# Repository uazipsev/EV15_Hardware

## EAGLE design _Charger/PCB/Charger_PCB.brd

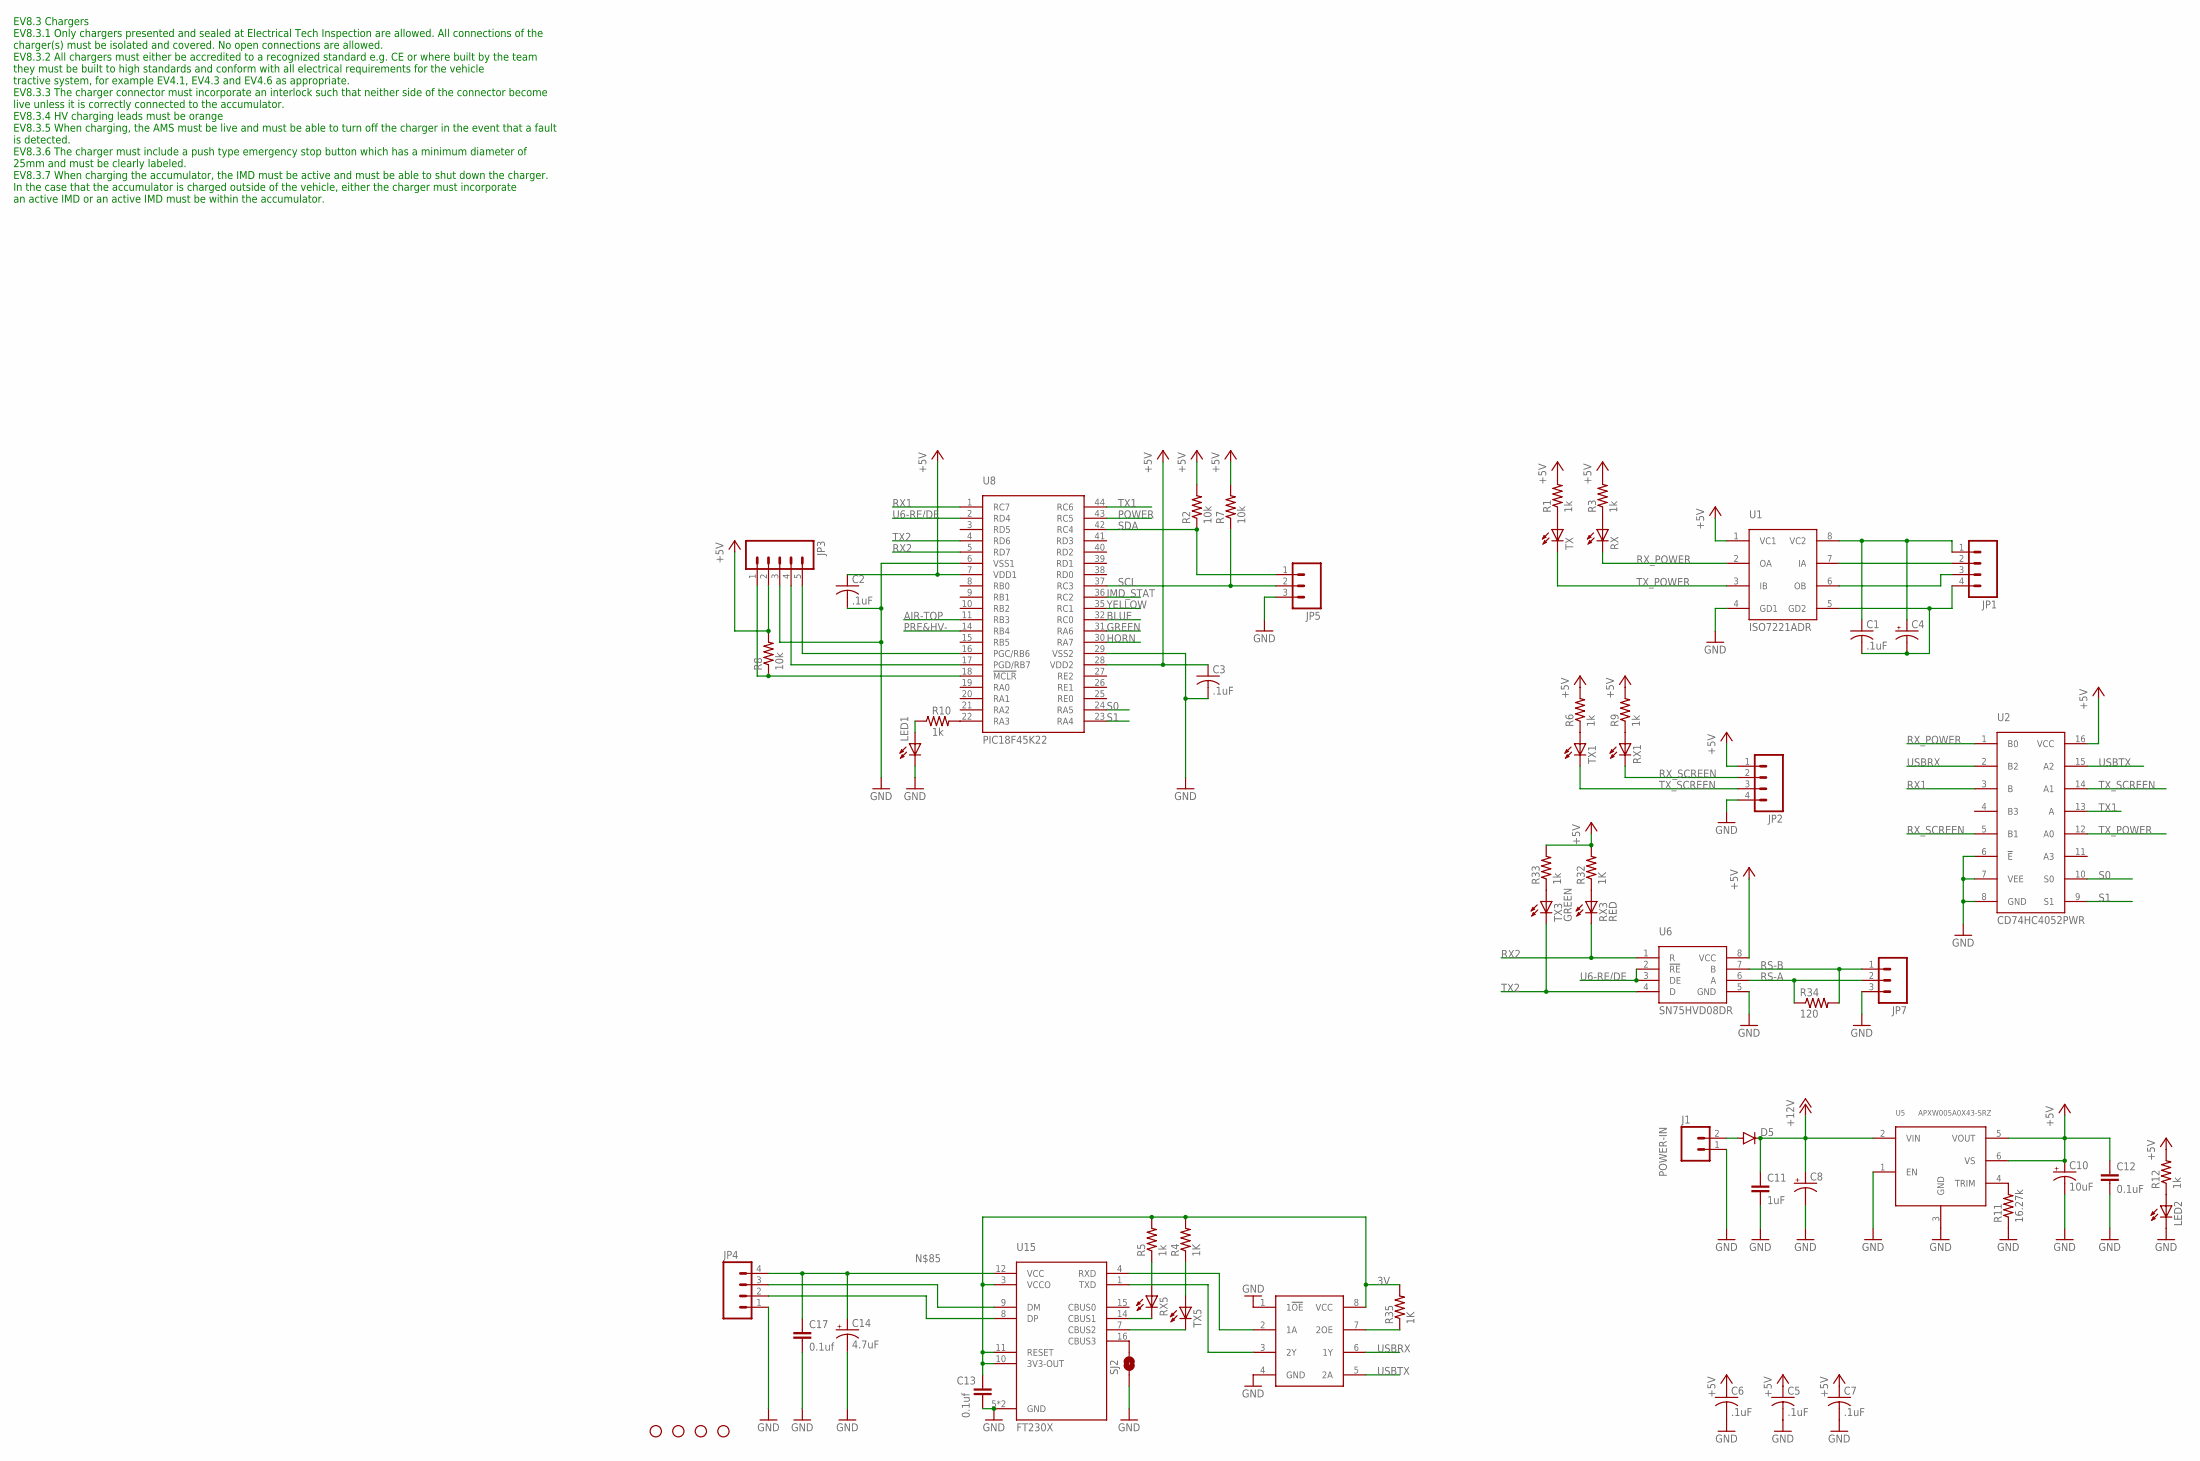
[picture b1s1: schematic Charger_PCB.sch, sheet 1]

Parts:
C1, C2, C3, C5, C6, C7: .1uF; C0805
C4: CAP_POL1206-KIT; EIA3216-KIT
C8: CAP_POLE; PANASONIC_E
C10: 10uF; EIA6032
C11: 1uF; 1206
C12: 0.1uF; 0805
C13, C17: 0.1uf; 0805
C14: 4.7uF; EIA3216
D5: DIODEHV; DIODE-HV
J1: POWER-IN; M2
JP1, JP2, JP4: M04POLAR_LOCK; MOLEX-1X4_LOCK
JP3: M05LOCK_LONGPADS; 1X05_LOCK_LONGPADS
JP5, JP7: M03POLAR_LOCK; MOLEX-1X3_LOCK
LED1: LEDCHIP-LED0805; CHIP-LED0805
LED2: LEDCHIPLED_0805; CHIPLED_0805
R1, R3, R5, R6, R9, R10, R12, R33: 1k; R0805
R2, R7: 10k; R0805
R4, R32, R35: 1K; R0805
R8: 10k; 0805
R11: 16.27k; R0805
R34: 120; R0805
RX, RX1, RX5: LEDCHIPLED_0805; CHIPLED_0805
RX3: RED; CHIPLED_0805
SJ2: JUMPER-PAD-2-NOYES_SILK; PAD-JUMPER-2-NO_YES_SILK
STANDOFF1, STANDOFF2, STANDOFF3, STANDOFF4: STAND-OFF
TX, TX1, TX5: LEDCHIPLED_0805; CHIPLED_0805
TX3: GREEN; CHIPLED_0805
U1: ISO7221ADR; SO08
U2: CD74HC4052PWR; TSSOP-16
U4: SN74LVC2G241DCTR; VFSOP-8
U5: APXW005A0X43-SRZ
U6: SN75HVD08DR; SO-8
U8: PIC18F45K22; TQFP-44
U15: FT230X; SSOP-16

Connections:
3V: C13.1, R4.2, R5.2, R35.2, U4.8 (VCC), U15.3 (VCCO), U15.10 (3V3-OUT), U15.11 (RESET)
+5V: C2.1, C3.1, C5.1, C6.1, C7.1, C10.P$1 (+), C12.1, JP2.1, JP3.2, R1.2, R2.2, R3.2, R6.2, R7.2, R8.2, R9.2, R12.2, R32.2, R33.2, U1.1 (VC1), U2.16 (VCC), U5.5 (VOUT), U5.6 (VS), U6.8 (VCC), U8.7 (VDD1), U8.28 (VDD2); also elsewhere on the board
+12V: C8.+, C11.1, D5.C, U5.2 (VIN); also elsewhere on the board
AIR-TOP: U8.11 (RB3); also elsewhere on the board
BLUE: U8.32 (RC0); also elsewhere on the board
GND: C2.2, C3.2, C5.2, C6.2, C7.2, C8.-, C10.P$2 (-), C11.2, C12.2, C13.2, C14.C (-), C17.2, J1.1, JP2.4, JP3.3, JP4.1, JP5.3, JP7.3, LED1.C, LED2.C, R11.1, SJ2.1, U1.4 (GD1), U2.6 (!E), U2.7 (VEE), U2.8 (GND), U4.1 (1!OE), U4.4 (GND), U5.1 (EN), U5.3 (GND), U6.5 (GND), U8.6 (VSS1), U8.29 (VSS2), U15.5 (GND), U15.13 (GND); also elsewhere on the board
GREEN: U8.31 (RA6); also elsewhere on the board
HORN: U8.30 (RA7); also elsewhere on the board
IMD_STAT: U8.36 (RC2); also elsewhere on the board
unnamed: LED1.A, R10.1
unnamed: R10.2, U8.22 (RA3)
unnamed: C1.1, C4.A (+), JP1.1, U1.8 (VC2)
unnamed: JP1.2, U1.7 (IA)
unnamed: JP1.3, U1.6 (OB)
unnamed: C1.2, C4.C (-), JP1.4, U1.5 (GD2)
unnamed: R1.1, TX.A
unnamed: R3.1, RX.A
unnamed: R4.1, TX5.A
unnamed: R5.1, RX5.A
unnamed: R6.1, TX1.A
unnamed: R9.1, RX1.A
unnamed: R11.2, U5.4 (TRIM)
unnamed: LED2.A, R12.1
unnamed: R33.1, TX3.A
unnamed: TX5.C, U15.7 (CBUS2)
unnamed: R32.1, RX3.A
unnamed: RX5.C, U15.14 (CBUS1)
unnamed: U4.2 (1A), U15.4 (RXD)
unnamed: JP3.4, U8.17 (PGD/RB7)
unnamed: U4.3 (2Y), U15.1 (TXD)
unnamed: JP4.3, U15.9 (DM)
unnamed: JP3.5, U8.16 (PGC/RB6)
unnamed: D5.A, J1.2
unnamed: JP3.1, R8.1, U8.18 (!MCLR)
unnamed: JP4.2, U15.8 (DP)
unnamed: SJ2.2, U15.16 (CBUS3)
unnamed: R35.1, U4.7 (2OE)
unnamed: C14.A (+), C17.1, JP4.4, U15.12 (VCC)
POWER: U8.43 (RC5); also elsewhere on the board
PRE&HV-: U8.14 (RB4); also elsewhere on the board
RS-A: JP7.2, R34.1, U6.6 (A)
RS-B: JP7.1, R34.2, U6.7 (B)
RX1: U2.3 (B), U8.1 (RC7)
RX2: RX3.C, U6.1 (R), U8.5 (RD7)
RX_POWER: RX.C, U1.2 (OA), U2.1 (B0)
RX_SCREEN: JP2.2, RX1.C, U2.5 (B1)
S0: U2.10 (S0), U8.24 (RA5)
S1: U2.9 (S1), U8.23 (RA4)
SCL: JP5.2, R7.1, U8.37 (RC3)
SDA: JP5.1, R2.1, U8.42 (RC4)
TX1: U2.13 (A), U8.44 (RC6)
TX2: TX3.C, U6.4 (D), U8.4 (RD6)
TX_POWER: TX.C, U1.3 (IB), U2.12 (A0)
TX_SCREEN: JP2.3, TX1.C, U2.14 (A1)
U6-RE/DE: U6.2 (!RE), U6.3 (DE), U8.2 (RD4)
USBRX: U2.2 (B2), U4.6 (1Y)
USBTX: U2.15 (A2), U4.5 (2A)
YELLOW: U8.35 (RC1); also elsewhere on the board

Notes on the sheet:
EV8.3 Chargers EV8.3.1 Only chargers presented and sealed at Electrical Tech Inspection are allowed. All connections of the charger(s) must be isolated and covered. No open connections are allowed. EV8.3.2 All chargers must either be accredited to a recognized standard e.g. CE or where built by the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

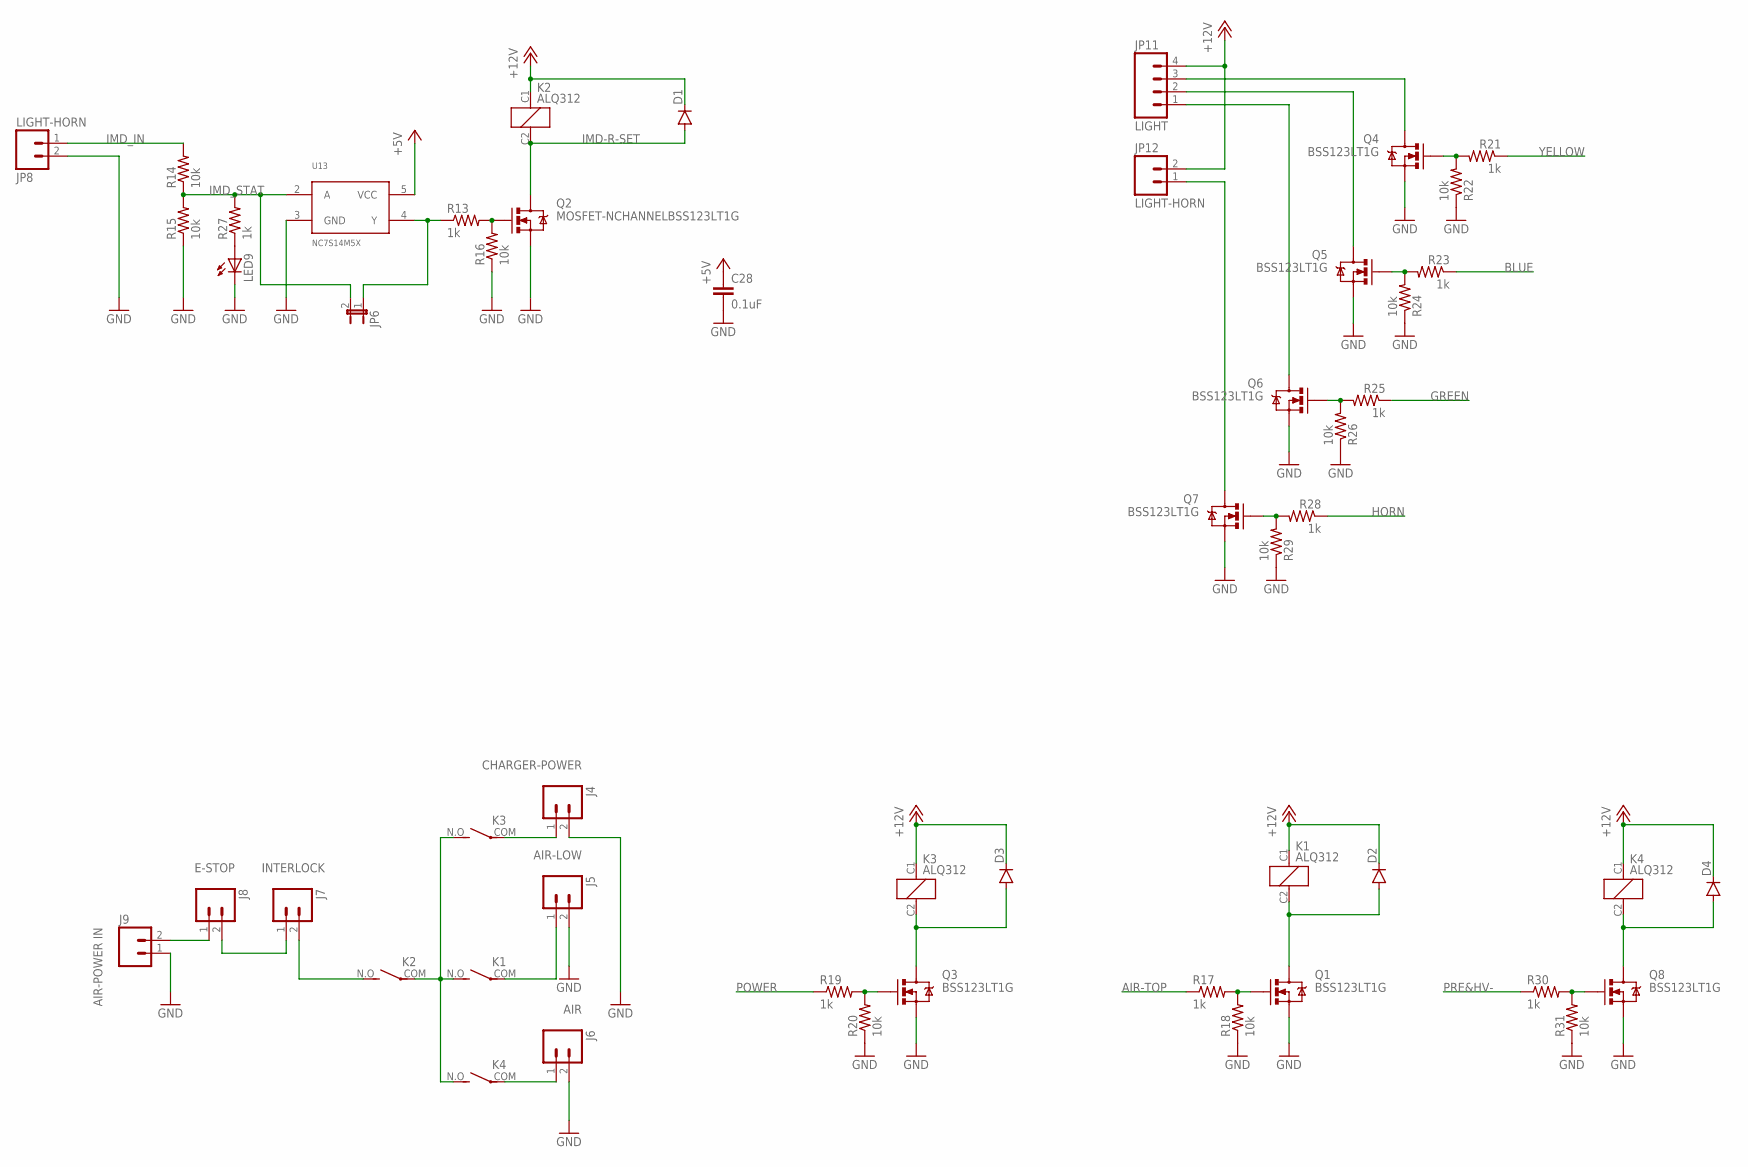
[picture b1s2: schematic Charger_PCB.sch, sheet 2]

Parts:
C28: 0.1uF; 0805
D1, D2, D3, D4: DIODEHV; DIODE-HV
J4: CHARGER-POWER; M2
J5: AIR-LOW; M2
J6: AIR; M2
J7: INTERLOCK; M2
J8: E-STOP; M2
J9: AIR-POWER IN; M2
JP6: JUMPER-2SMD-NO; SJ_2S-NO
JP8, JP12: LIGHT-HORN; MOLEX-1X2_LOCK
JP11: LIGHT; MOLEX-1X4_LOCK
K1, K2, K3, K4: ALQ312
LED9: LEDCHIPLED_0805; CHIPLED_0805
Q1, Q3, Q4, Q5, Q6, Q7, Q8: BSS123LT1G; SOT23
Q2: MOSFET-NCHANNELBSS123LT1G; SOT23
R13, R17, R19, R21, R23, R25, R27, R28, R30: 1k; 0805
R14, R15, R16, R18, R20, R22, R24, R26, R29, R31: 10k; 0805
U13: NC7S14M5X; SOT23-5

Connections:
+5V: C28.1, U13.5 (VCC); also elsewhere on the board
+12V: D1.C, D2.C, D3.C, D4.C, JP11.4, JP12.2, K1.C1 (+), K2.C1 (+), K3.C1 (+), K4.C1 (+); also elsewhere on the board
AIR-TOP: R17.1; also elsewhere on the board
BLUE: R23.1; also elsewhere on the board
GND: C28.2, J4.2, J5.2, J6.2, J9.1, JP8.2, LED9.C, Q1.2 (S), Q2.2 (S), Q3.2 (S), Q4.2 (S), Q5.2 (S), Q6.2 (S), Q7.2 (S), Q8.2 (S), R15.1, R16.1, R18.1, R20.1, R22.1, R24.1, R26.1, R29.1, R31.1, U13.3 (GND); also elsewhere on the board
GREEN: R25.1; also elsewhere on the board
HORN: R28.1; also elsewhere on the board
IMD-R-SET: D1.A, K2.C2 (-), Q2.3 (D)
IMD-R-SET1: D2.A, K1.C2 (-), Q1.3 (D)
IMD-R-SET2: D3.A, K3.C2 (-), Q3.3 (D)
IMD-R-SET3: D4.A, K4.C2 (-), Q8.3 (D)
IMD_IN: JP8.1, R14.2
IMD_STAT: JP6.2, R14.1, R15.2, R27.2, U13.2 (A); also elsewhere on the board
unnamed: K1.N.O (S), K2.COM, K3.N.O (S), K4.N.O (S)
unnamed: Q2.1 (G), R13.2, R16.2
unnamed: Q8.1 (G), R30.2, R31.2
unnamed: J8.1, J9.2
unnamed: J7.1, J8.2
unnamed: J4.1, K3.COM
unnamed: Q4.1 (G), R21.2, R22.2
unnamed: J6.1, K4.COM
unnamed: Q1.1 (G), R17.2, R18.2
unnamed: Q3.1 (G), R19.2, R20.2
unnamed: Q5.1 (G), R23.2, R24.2
unnamed: Q6.1 (G), R25.2, R26.2
unnamed: Q7.1 (G), R28.2, R29.2
unnamed: JP11.3, Q4.3 (D)
unnamed: JP11.2, Q5.3 (D)
unnamed: JP11.1, Q6.3 (D)
unnamed: JP6.1, R13.1, U13.4 (Y)
unnamed: LED9.A, R27.1
unnamed: JP12.1, Q7.3 (D)
unnamed: J5.1, K1.COM
unnamed: J7.2, K2.N.O (S)
POWER: R19.1; also elsewhere on the board
PRE&HV-: R30.1; also elsewhere on the board
YELLOW: R21.1; also elsewhere on the board

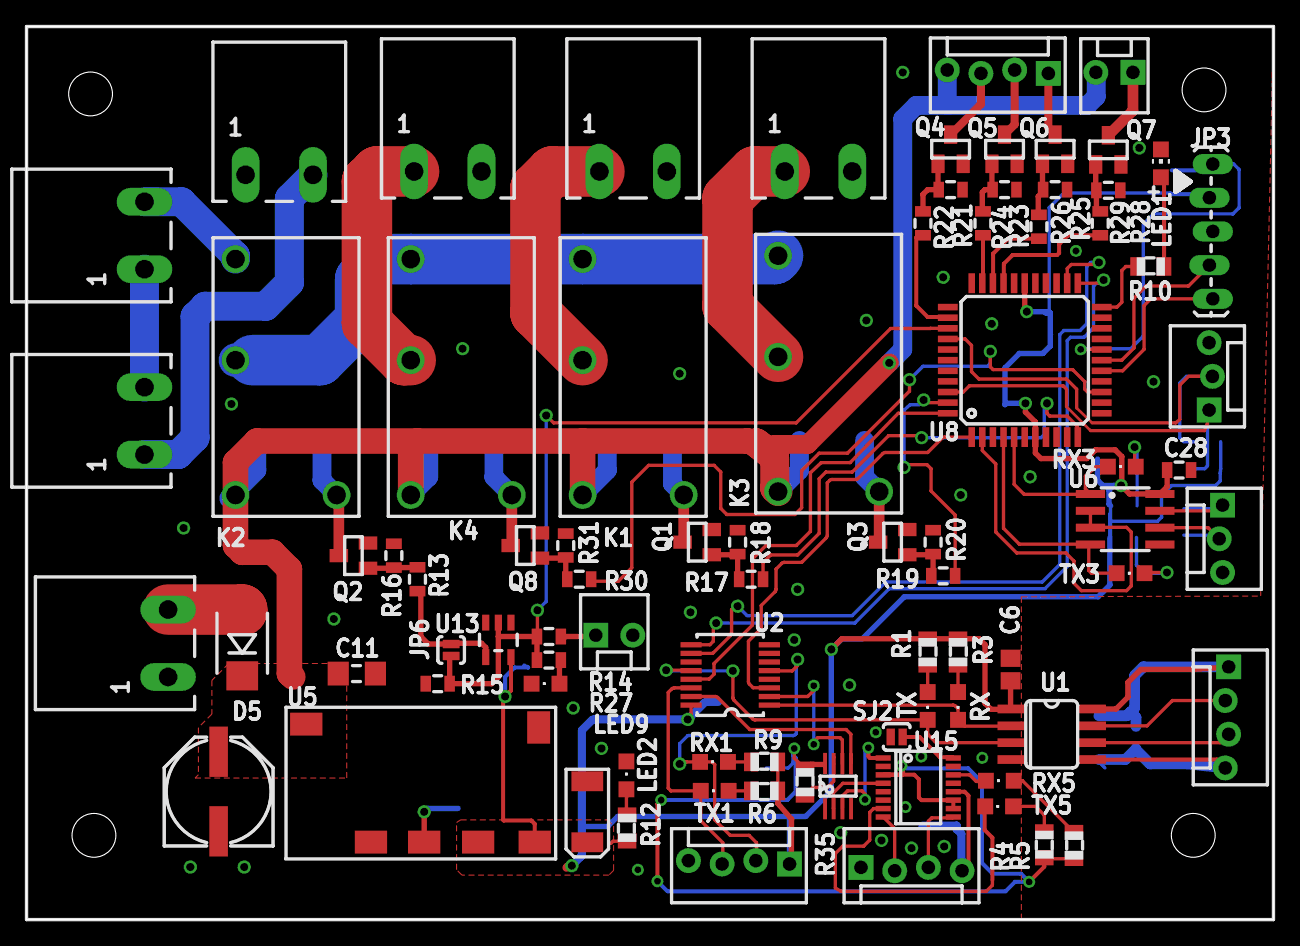
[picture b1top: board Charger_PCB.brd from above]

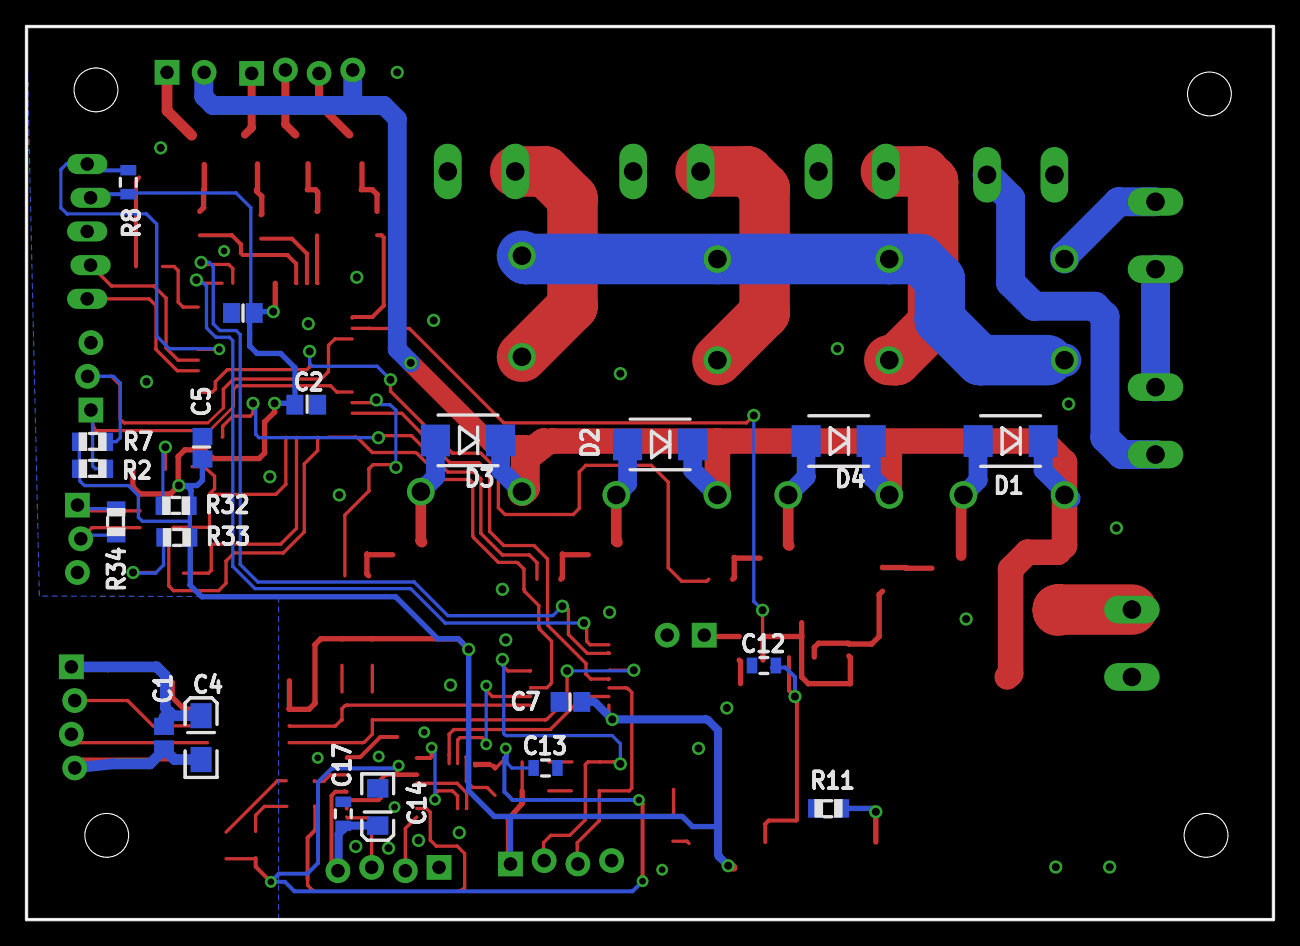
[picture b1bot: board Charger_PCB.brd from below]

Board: 2 copper layers, 94.0 x 67.3 mm, 108 parts (21 on the bottom side), 84 nets.

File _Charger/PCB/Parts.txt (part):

Partlist

Exported from Charger_PCB.sch at 5/25/2015 11:38:13 PM

EAGLE Version 6.6.0 Copyright (c) 1988-2014 CadSoft

Assembly variant: 

Part     Value                     Device                    Package                  Library               Sheet

C1       .1uF                      C-USC0805                 C0805                    adafruit              1
C2       .1uF                      C-USC0805                 C0805                    adafruit              1
C3       .1uF                      C-USC0805                 C0805                    adafruit              1
C4                                 CAP_POL1206-KIT           EIA3216-KIT              SparkFun-Passives     1
C5       .1uF                      C-USC0805                 C0805                    adafruit              1
C6       .1uF                      C-USC0805                 C0805                    adafruit              1
C7       .1uF                      C-USC0805                 C0805                    adafruit              1
C8                                 CAP_POLE                  PANASONIC_E              SparkFun-Capacitors   1
C10      10uF                      CAP_POL6032               EIA6032                  SparkFun-Capacitors   1
C11      1uF                       CAP1206                   1206                     SparkFun-Capacitors   1
C12      0.1uF                     CAP0805                   0805                     SparkFun-Capacitors   1
C13      0.1uf                     CAP0805                   0805                     SparkFun              1
C14      4.7uF                     CAP_POL1206               EIA3216                  SparkFun              1
C17      0.1uf                     CAP0805                   0805                     SparkFun              1
C28      0.1uF                     CAP0805                   0805                     SparkFun-Passives     2
D1                                 DIODEHV                   DIODE-HV                 SparkFun-DiscreteSemi 2
D2                                 DIODEHV                   DIODE-HV                 SparkFun-DiscreteSemi 2
D3                                 DIODEHV                   DIODE-HV                 SparkFun-DiscreteSemi 2
D4                                 DIODEHV                   DIODE-HV                 SparkFun-DiscreteSemi 2
D5                                 DIODEHV                   DIODE-HV                 SparkFun-DiscreteSemi 1
J1       POWER-IN                  EUROMAG-290DEG            M2                       NASA_LIB              1
J4       CHARGER-POWER             EUROMAG-290DEG            M2                       NASA_LIB              2
J5       AIR-LOW                   EUROMAG-290DEG            M2                       NASA_LIB              2
J6       AIR                       EUROMAG-290DEG            M2                       NASA_LIB              2
J7       INTERLOCK                 EUROMAG-290DEG            M2                       NASA_LIB              2
J8       E-STOP                    EUROMAG-290DEG            M2                       NASA_LIB              2
J9       AIR-POWER IN              EUROMAG-290DEG            M2                       NASA_LIB              2
JP1                                M04POLAR_LOCK             MOLEX-1X4_LOCK           SparkFun-Connectors   1
JP2                                M04POLAR_LOCK             MOLEX-1X4_LOCK           SparkFun-Connectors   1
JP3                                M05LOCK_LONGPADS          1X05_LOCK_LONGPADS       SparkFun-Connectors   1
JP4                                M04POLAR_LOCK             MOLEX-1X4_LOCK           SparkFun-Connectors   1
JP5                                M03POLAR_LOCK             MOLEX-1X3_LOCK           SparkFun-Connectors   1
JP6                                JUMPER-2SMD-NO            SJ_2S-NO                 SparkFun-Passives     2
JP7                                M03POLAR_LOCK             MOLEX-1X3_LOCK           SparkFun-Connectors   1
JP8      LIGHT-HORN                M02POLAR_LOCK             MOLEX-1X2_LOCK           SparkFun-Connectors   2
JP11     LIGHT                     M04POLAR_LOCK             MOLEX-1X4_LOCK           SparkFun-Connectors   2
JP12     LIGHT-HORN                M02POLAR_LOCK             MOLEX-1X2_LOCK           SparkFun-Connectors   2
K1       ALQ312                    ALQ312                    ALQ312                   FSAE Eletric (2)      2
K2       ALQ312                    ALQ312                    ALQ312                   FSAE Eletric (2)      2
K3       ALQ312                    ALQ312                    ALQ312                   FSAE Eletric (2)      2
K4       ALQ312                    ALQ312                    ALQ312                   FSAE Eletric          2
LED1                               LEDCHIP-LED0805           CHIP-LED0805             adafruit              1
LED2                               LEDCHIPLED_0805           CHIPLED_0805             adafruit              1
LED9                               LEDCHIPLED_0805           CHIPLED_0805             adafruit              2
Q1       BSS123LT1G                MOSFET-NCHANNELBSS123LT1G SOT23                    SparkFun-DiscreteSemi 2
Q2       MOSFET-NCHANNELBSS123LT1G MOSFET-NCHANNELBSS123LT1G SOT23                    SparkFun-DiscreteSemi 2
Q3       BSS123LT1G                MOSFET-NCHANNELBSS123LT1G SOT23                    SparkFun-DiscreteSemi 2
Q4       BSS123LT1G                MOSFET-NCHANNELBSS123LT1G SOT23                    SparkFun-DiscreteSemi 2
Q5       BSS123LT1G                MOSFET-NCHANNELBSS123LT1G SOT23                    SparkFun-DiscreteSemi 2
Q6       BSS123LT1G                MOSFET-NCHANNELBSS123LT1G SOT23                    SparkFun-DiscreteSemi 2
Q7       BSS123LT1G                MOSFET-NCHANNELBSS123LT1G SOT23                    SparkFun-DiscreteSemi 2
Q8       BSS123LT1G                MOSFET-NCHANNELBSS123LT1G SOT23                    SparkFun-DiscreteSemi 2
R1       1k                        R-US_R0805                R0805                    adafruit              1
R2       2k                        R-US_R0805                R0805                    adafruit              1
R3       1k                        R-US_R0805                R0805                    adafruit              1
R4       1K                        R-US_R0805                R0805                    adafruit              1
R5       1k                        R-US_R0805                R0805                    adafruit              1
R6       1k                        R-US_R0805                R0805                    adafruit              1
R7       2k                        R-US_R0805                R0805                    adafruit              1
R8       10k                       RESISTOR0805-RES          0805                     SparkFun-Passives     1
R9       1k                        R-US_R0805                R0805                    adafruit              1
R10      1k                        R-US_R0805                R0805                    adafruit              1
R11      16.27k                    R-US_R0805                R0805                    adafruit              1
R12      1k                        R-US_R0805                R0805                    adafruit              1
R13      1k                        RESISTOR0805-RES          0805                     SparkFun-Passives     2
R14      5k                        RESISTOR0805-RES          0805                     SparkFun-Passives     2
R15      5k                        RESISTOR0805-RES          0805                     SparkFun-Passives     2
R16      10k                       RESISTOR0805-RES          0805                     SparkFun-Passives     2
R17      1k                        RESISTOR0805-RES          0805                     SparkFun-Passives     2
R18      10k                       RESISTOR0805-RES          0805                     SparkFun-Passives     2
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
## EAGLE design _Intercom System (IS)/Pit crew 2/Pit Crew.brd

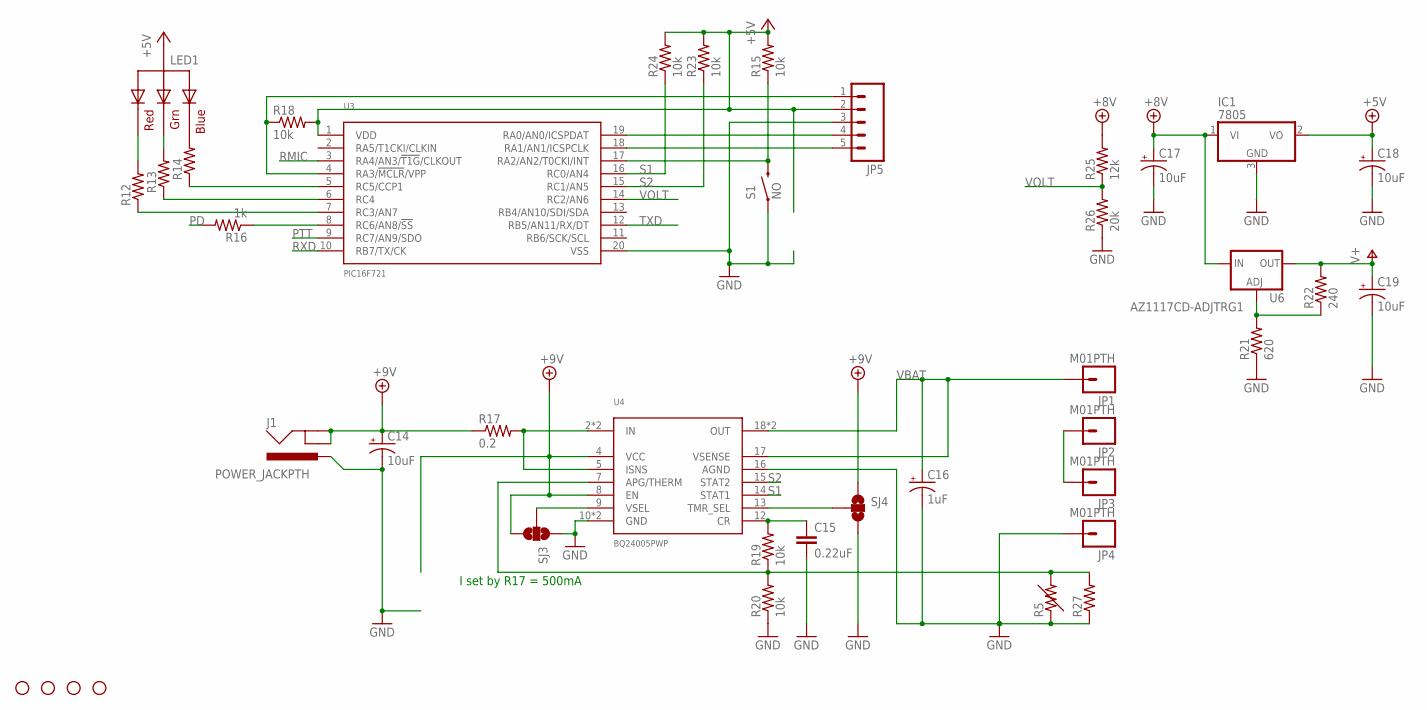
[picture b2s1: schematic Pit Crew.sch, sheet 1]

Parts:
C14, C17, C18, C19: 10uF; EIA3216
C15: 0.22uF; 0805
C16: 1uF; EIA3216
IC1: 7805; TO252
J1: POWER_JACKPTH; POWER_JACK_PTH
JP1, JP2, JP3, JP4: M01PTH; 1X01
JP5: M05LOCK_LONGPADS; 1X05_LOCK_LONGPADS
LED1: RGBLED_CA-5MM; LED5MMRGB
R5, R12, R13, R14: RESISTOR0805-RES; 0805
R15, R19, R20, R23, R24: 10k; 0805
R16: 1k; 0805
R17: 0.2; R2512
R18: 10k; R0805
R21: 620; 0805
R22: 240; 0805
R25: 12k; 0805
R26: 20k; 0805
R27: R-US_0207/7; 0207/7
S1: NO; TACTILE-PTH-SIDEEZ
SJ3, SJ4: SOLDERJUMPER_2WAYS; SJ_3
STANDOFF1, STANDOFF2, STANDOFF3, STANDOFF4: STAND-OFF
U3: PIC16F721; SSOP-20
U4: BQ24005PWP; HTSSOP-20
U6: AZ1117CD-ADJTRG1; V-REG_DPACK

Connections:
+5V: C18.A (+), IC1.2 (VO), JP5.2, LED1.2 (VCC), R15.2, R18.2, R23.2, R24.2, U3.1 (VDD); also elsewhere on the board
+8V: C17.A (+), IC1.1 (VI), R25.2, U6.3 (IN); also elsewhere on the board
+9V: C14.A (+), J1.GND, J1.GNDBREAK, R17.1, SJ3.3, SJ4.1, U4.4 (VCC), U4.8 (EN)
GND: C14.C (-), C15.2, C16.C (-), C17.C (-), C18.C (-), C19.C (-), IC1.3 (GND), J1.PWR, JP4.1, JP5.3, R5.1, R20.1, R21.1, R26.1, R27.1, S1.1, SJ3.1, SJ4.3, U3.20 (VSS), U4.10 (GND), U4.16 (AGND), U4.EP (GND); also elsewhere on the board
unnamed: LED1.1 (RED), R12.2
unnamed: LED1.4 (BLUE), R14.2
unnamed: LED1.3 (GREEN), R13.2
unnamed: JP2.1, JP3.1
unnamed: R14.1, U3.5 (RC5/CCP1)
unnamed: R13.1, U3.6 (RC4)
unnamed: R12.1, U3.7 (RC3/AN7)
unnamed: R15.1, S1.2, U3.17 (RA2/AN2/T0CKI/INT)
unnamed: R16.1, U3.8 (RC6/AN8/!SS!)
unnamed: JP5.1, R18.1, U3.4 (RA3/!MCLR!/VPP)
unnamed: JP5.4, U3.19 (RA0/AN0/ICSPDAT)
unnamed: JP5.5, U3.18 (RA1/AN1/ICSPCLK)
unnamed: R17.2, U4.2 (IN), U4.3 (IN), U4.5 (ISNS)
unnamed: R21.2, R22.1, U6.1 (ADJ)
unnamed: SJ3.2, U4.9 (VSEL)
unnamed: R5.2, R19.1, R20.2, R27.2, U4.7 (APG/THERM)
unnamed: C15.1, R19.2, U4.12 (CR)
unnamed: SJ4.2, U4.13 (TMR_SEL)
PD: R16.2; also elsewhere on the board
PTT: U3.9 (RC7/AN9/SDO); also elsewhere on the board
RMIC: U3.3 (RA4/AN3/!T1G!/CLKOUT); also elsewhere on the board
RXD: U3.10 (RB7/TX/CK); also elsewhere on the board
S1: R24.1, U3.16 (RC0/AN4), U4.14 (STAT1)
S2: R23.1, U3.15 (RC1/AN5), U4.15 (STAT2)
TXD: U3.12 (RB5/AN11/RX/DT); also elsewhere on the board
V+: C19.A (+), R22.2, U6.4 (OUT); also elsewhere on the board
VBAT: C16.A (+), JP1.1, U4.17 (VSENSE), U4.18 (OUT), U4.19 (OUT); also elsewhere on the board
VOLT: R25.1, R26.2, U3.14 (RC2/AN6)

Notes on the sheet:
I set by R17 = 500mA

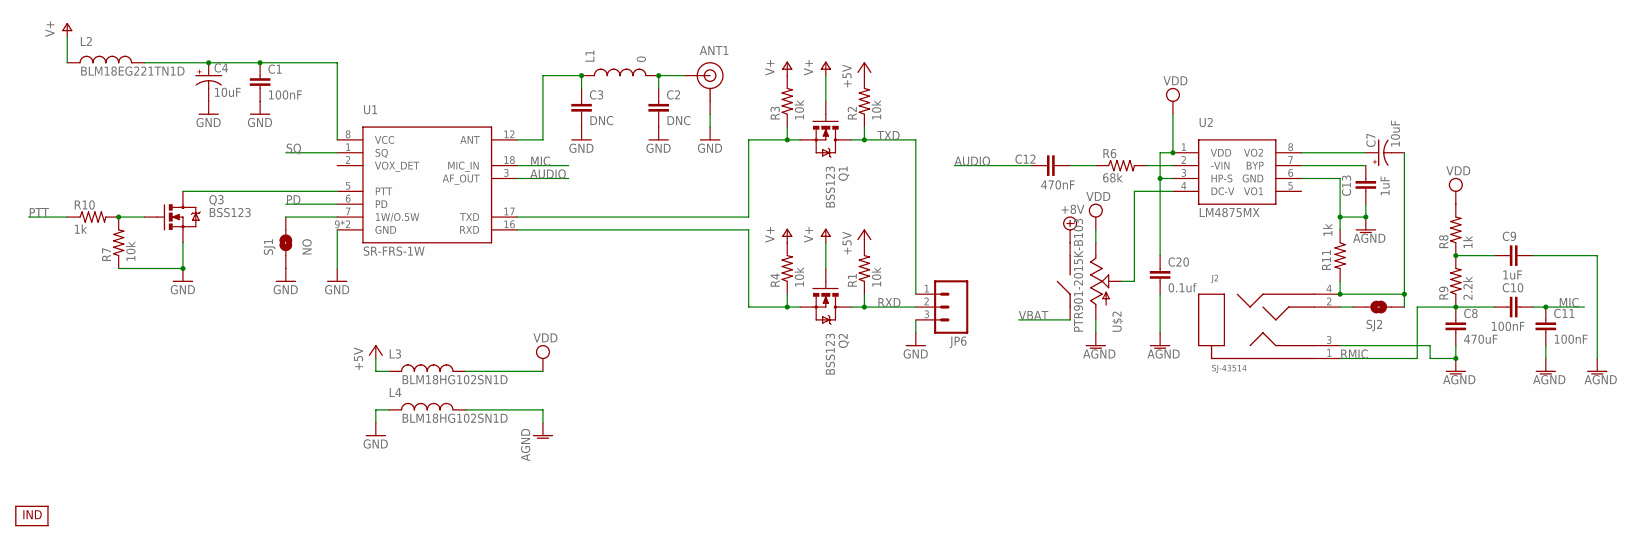
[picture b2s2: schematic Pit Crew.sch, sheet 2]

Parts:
ANT1: SMA; CONSMA002
C1, C10, C11: 100nF; 0805
C2, C3: DNC; 0805
C4, C7: 10uF; EIA3216
C8: 470uF; 0805
C9, C13: 1uF; 0805
C12: 470nF; 0805
C20: 0.1uf; 0805
J2: SJ-43514
JP6: M03LOCK; 1X03_LOCK
L1: 0; 1007
L2: BLM18EG221TN1D; 0603
L3, L4: BLM18HG102SN1D; 0603
Q1, Q2, Q3: BSS123; SOT23
R1, R2, R3, R4, R7: 10k; 0805
R6: 68k; 0805
R8, R10, R11: 1k; 0805
R9: 2.2k; 0805
SJ1: NO; SJ_2S-NO
SJ2: SOLDERJUMPERNO; SJ_2S-NO
U1: SR-FRS-1W
U2: LM4875MX; SO-8
U$2: PTR901-2015K-B103
U$3: INDPK1; PICKIT-PIN-1

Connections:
+5V: L3.1, R1.2, R2.2; also elsewhere on the board
+8V: U$2.S1; also elsewhere on the board
AGND: C8.2, C9.2, C11.2, C13.1, C20.2, J2.3, L4.2, R11.1, U2.6 (GND), U$2.1 (CCW)
AUDIO: C12.1, U1.3 (AF_OUT)
GND: ANT1.1 (GND), ANT1.2 (GND), ANT1.3 (GND), ANT1.4 (GND), C1.2, C2.2, C3.2, C4.C (-), JP6.3, L4.1, Q3.2 (S), R7.1, SJ1.1, U1.9 (GND), U1.10 (GND); also elsewhere on the board
MIC: C10.2, C11.1, U1.18 (MIC_IN)
unnamed: C3.1, L1.1, U1.12 (ANT)
unnamed: ANT1.C (SIGNAL), C2.1, L1.2
unnamed: C1.1, C4.A (+), L2.2, U1.8 (VCC)
unnamed: SJ1.2, U1.7 (1W/O.5W)
unnamed: J2.2, SJ2.1
unnamed: U2.4 (DC-V), U$2.2 (W)
unnamed: Q2.2 (S), R4.1, U1.16 (RXD)
unnamed: Q1.2 (S), R3.1, U1.17 (TXD)
unnamed: C13.2, U2.7 (BYP)
unnamed: C12.2, R6.1
unnamed: R6.2, U2.2 (-VIN)
unnamed: C9.1, R8.1, R9.2
unnamed: C7.A (+), U2.8 (VO2)
unnamed: Q3.1 (G), R7.2, R10.2
unnamed: C7.C (-), J2.4, R11.2, SJ2.2
PD: U1.6 (PD); also elsewhere on the board
PTT: R10.1; also elsewhere on the board
PTT-1: Q3.3 (D), U1.5 (PTT)
RMIC: C8.1, C10.1, J2.1, R9.1; also elsewhere on the board
RXD: JP6.2, Q2.3 (D), R1.1; also elsewhere on the board
SQ: U1.1 (SQ)
TXD: JP6.1, Q1.3 (D), R2.1; also elsewhere on the board
V+: L2.1, Q1.1 (G), Q2.1 (G), R3.2, R4.2; also elsewhere on the board
VBAT: U$2.S2; also elsewhere on the board
VDD: C20.1, L3.2, R8.2, U2.1 (VDD), U2.3 (HP-S), U$2.3 (CW)

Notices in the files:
parts and their libraries:
SparkFun: Licensing: CC v3.0 Share-Alike You are welcome to use this library for commercial purposes.
SparkFun-Passives: Licensing: Creative Commons ShareAlike 4.0 International - https://creativecommons.org/licenses/by-sa/4.0
